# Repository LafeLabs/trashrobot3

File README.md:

# trashrobot3
this is the trash robot that finally pulls the Five Boards into one directory so it's not all over the place

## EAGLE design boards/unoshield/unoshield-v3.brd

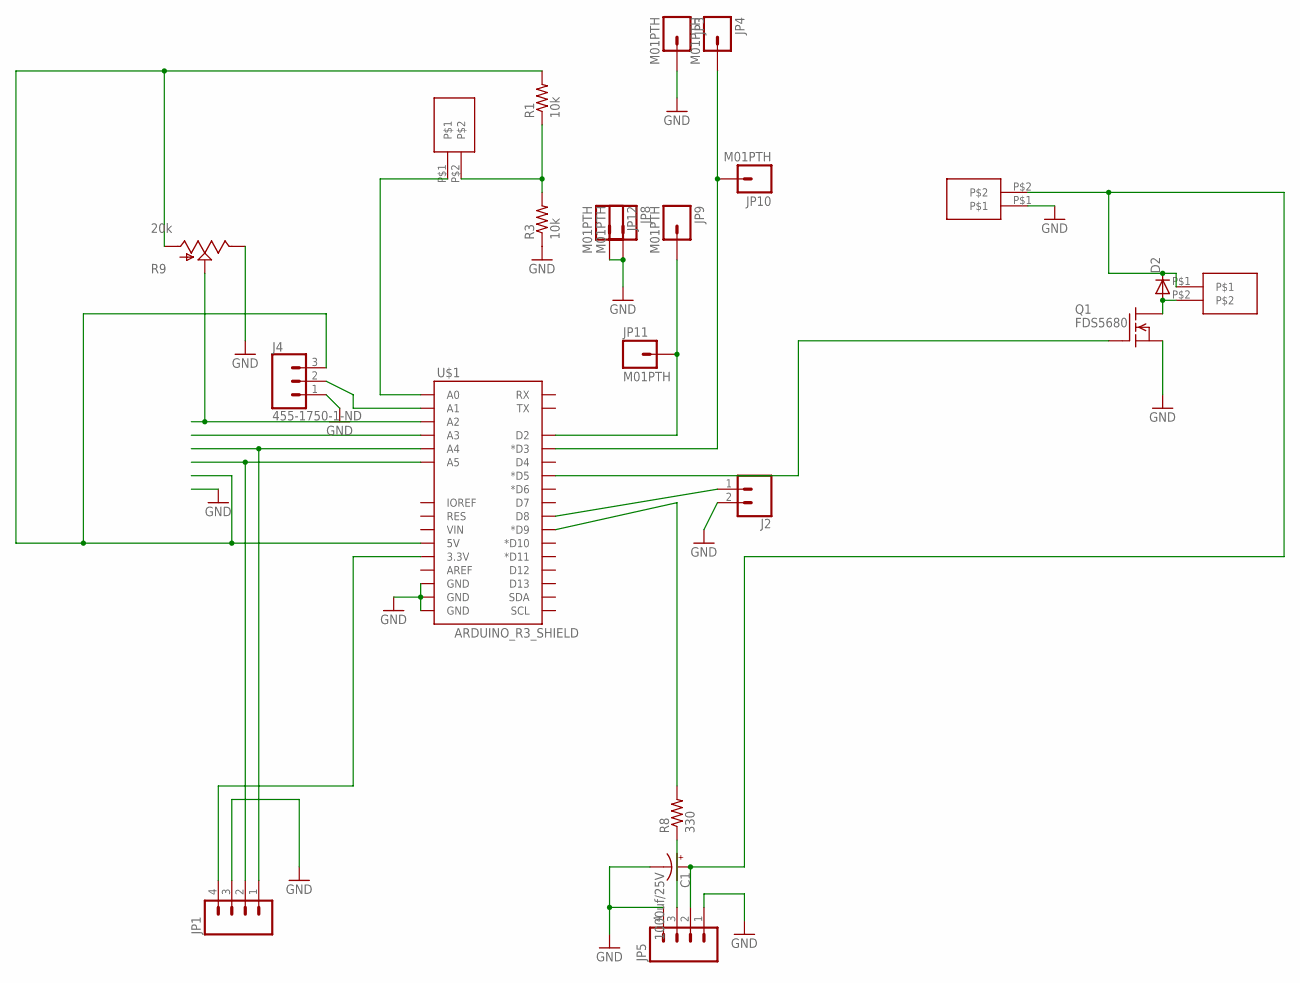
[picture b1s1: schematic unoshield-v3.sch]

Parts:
C1: 1000uf/25V; CPOL-RADIAL-1000UF-25V-KIT
D2: DIODE-DO-214AC; DO-214AC
J2: CONN_02; 1X02
J4: 455-1750-1-ND; 1X03
JP1, JP5: M04PTH; 1X04
JP3, JP4, JP8, JP9, JP10, JP11, JP12: M01PTH; 1X01
Q1: FDS5680; SO-8
R1, R3: 10k; R0603
R8: 330; R0603
R9: 20k; ALPS_POT_KIT
U$1: ARDUINO_R3_SHIELD; UNO_R3_SHIELD
U$6: SPRING-TERMINAL
X1, X2: SPRING-TERMINAL

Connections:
5V: J4.3, R1.2, R9.P$3 (A), U$1.5V
BUTTON: JP4.1, JP10.1, U$1.D3 (*D3)
CL: JP1.2, U$1.A5
DA: JP1.1, U$1.A4
GND: C1.-, J2.2, J4.1, JP1.3, JP3.1, JP5.1, JP5.4, JP8.1, JP12.1, Q1.1 (S), Q1.2 (S), Q1.3 (S), R3.1, R9.P$1 (E), U$1.GND@0 (GND), U$1.GND@1 (GND), U$1.GND@2 (GND), X1.P$1; also elsewhere on the board
unnamed 5: Q1.4 (G), U$1.D5 (*D5); also elsewhere on the board
unnamed: R8.2, U$1.D9 (*D9)
unnamed: R1.1, R3.2, X2.P$2
unnamed: J4.2, U$1.A1
unnamed: D2.A, Q1.5 (D), Q1.6 (D), Q1.7 (D), Q1.8 (D), U$6.P$2
unnamed: JP9.1, JP11.1, U$1.D2
unnamed: J2.1, U$1.D8
unnamed: U$1.A0, X2.P$1
unnamed: JP5.3, R8.1
unnamed: R9.P$2 (S), U$1.A2
VCC: JP1.4, U$1.3.3V
VIN: C1.+, D2.C, JP5.2, U$6.P$1, X1.P$2

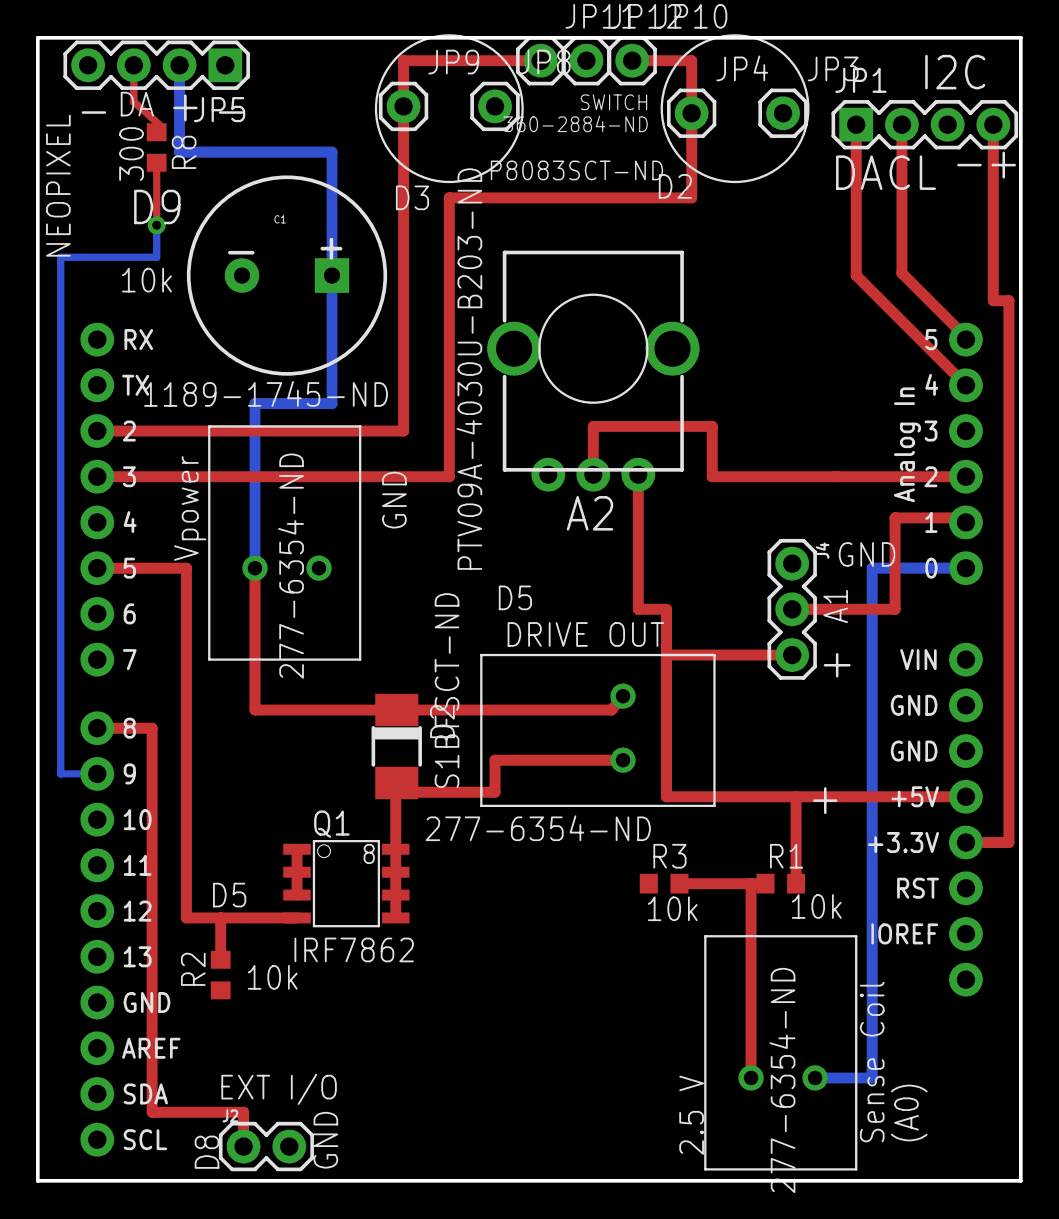
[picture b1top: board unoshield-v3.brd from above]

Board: 2 copper layers, 54.6 x 63.5 mm, 23 parts (0 on the bottom side), 17 nets.

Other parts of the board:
R2: 10k; R0603

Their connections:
GND: R2.1; also elsewhere on the board
unnamed 5: R2.2; also elsewhere on the board

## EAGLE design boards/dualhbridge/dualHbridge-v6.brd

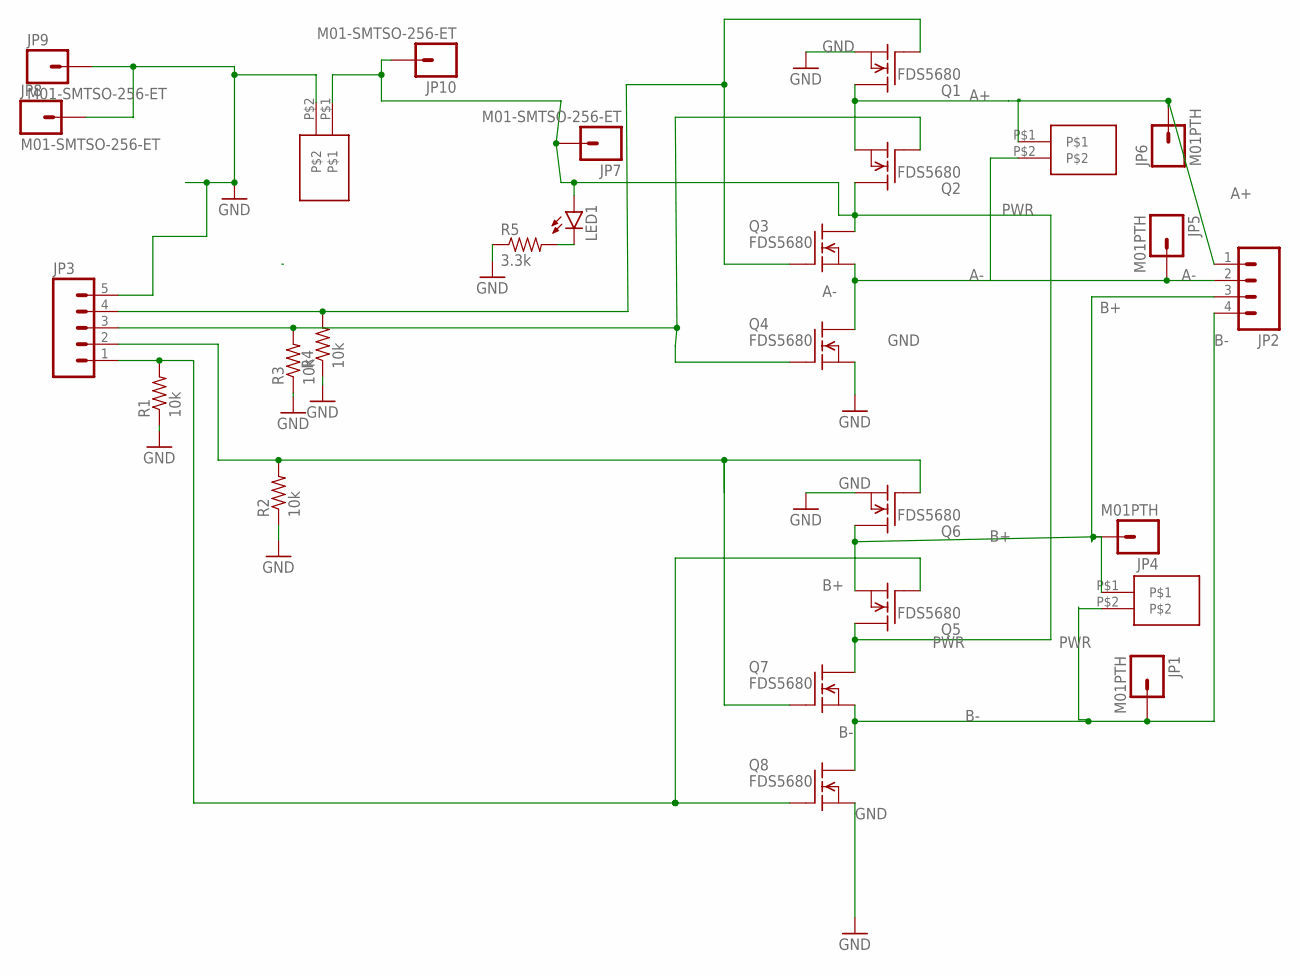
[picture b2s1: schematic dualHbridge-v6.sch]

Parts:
JP1, JP4, JP5, JP6: M01PTH; 1X01@1
JP2: M04LONGPADS; 1X04_LONGPADS
JP3: M05PTH; 1X05
JP7, JP8, JP9, JP10: M01-SMTSO-256-ET; SMTSO-256-ET
LED1: LED5MM
Q1, Q2, Q3, Q4, Q5, Q6, Q7, Q8: FDS5680; SO-8
R1, R2, R3, R4: 10k; 0603-RES
R5: 3.3k; 0603-RES
U$1, U$2, U$3: SPRING-TERMINAL

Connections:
A+: JP2.1, JP6.1, Q1.5 (D), Q1.6 (D), Q1.7 (D), Q1.8 (D), Q2.1 (S), Q2.2 (S), Q2.3 (S), U$1.P$1
A-: JP2.2, JP5.1, Q3.1 (S), Q3.2 (S), Q3.3 (S), Q4.5 (D), Q4.6 (D), Q4.7 (D), Q4.8 (D), U$1.P$2
B+: JP2.3, JP4.1, Q5.1 (S), Q5.2 (S), Q5.3 (S), Q6.5 (D), Q6.6 (D), Q6.7 (D), Q6.8 (D), U$3.P$1
B-: JP1.1, JP2.4, Q7.1 (S), Q7.2 (S), Q7.3 (S), Q8.5 (D), Q8.6 (D), Q8.7 (D), Q8.8 (D), U$3.P$2
GND: JP3.5, JP8.P$1, JP9.P$1, Q1.1 (S), Q1.2 (S), Q1.3 (S), Q4.1 (S), Q4.2 (S), Q4.3 (S), Q6.1 (S), Q6.2 (S), Q6.3 (S), Q8.1 (S), Q8.2 (S), Q8.3 (S), R1.1, R2.1, R3.1, R4.1, R5.1, U$2.P$2
unnamed: JP3.3, Q2.4 (G), Q4.4 (G), R3.2
unnamed: JP3.4, Q1.4 (G), Q3.4 (G), R4.2
unnamed: LED1.K (C), R5.2
unnamed: JP3.2, Q6.4 (G), Q7.4 (G), R2.2
unnamed: JP3.1, Q5.4 (G), Q8.4 (G), R1.2
PWR: JP7.P$1, JP10.P$1, LED1.A, Q2.5 (D), Q2.6 (D), Q2.7 (D), Q2.8 (D), Q3.5 (D), Q3.6 (D), Q3.7 (D), Q3.8 (D), Q5.5 (D), Q5.6 (D), Q5.7 (D), Q5.8 (D), Q7.5 (D), Q7.6 (D), Q7.7 (D), Q7.8 (D), U$2.P$1

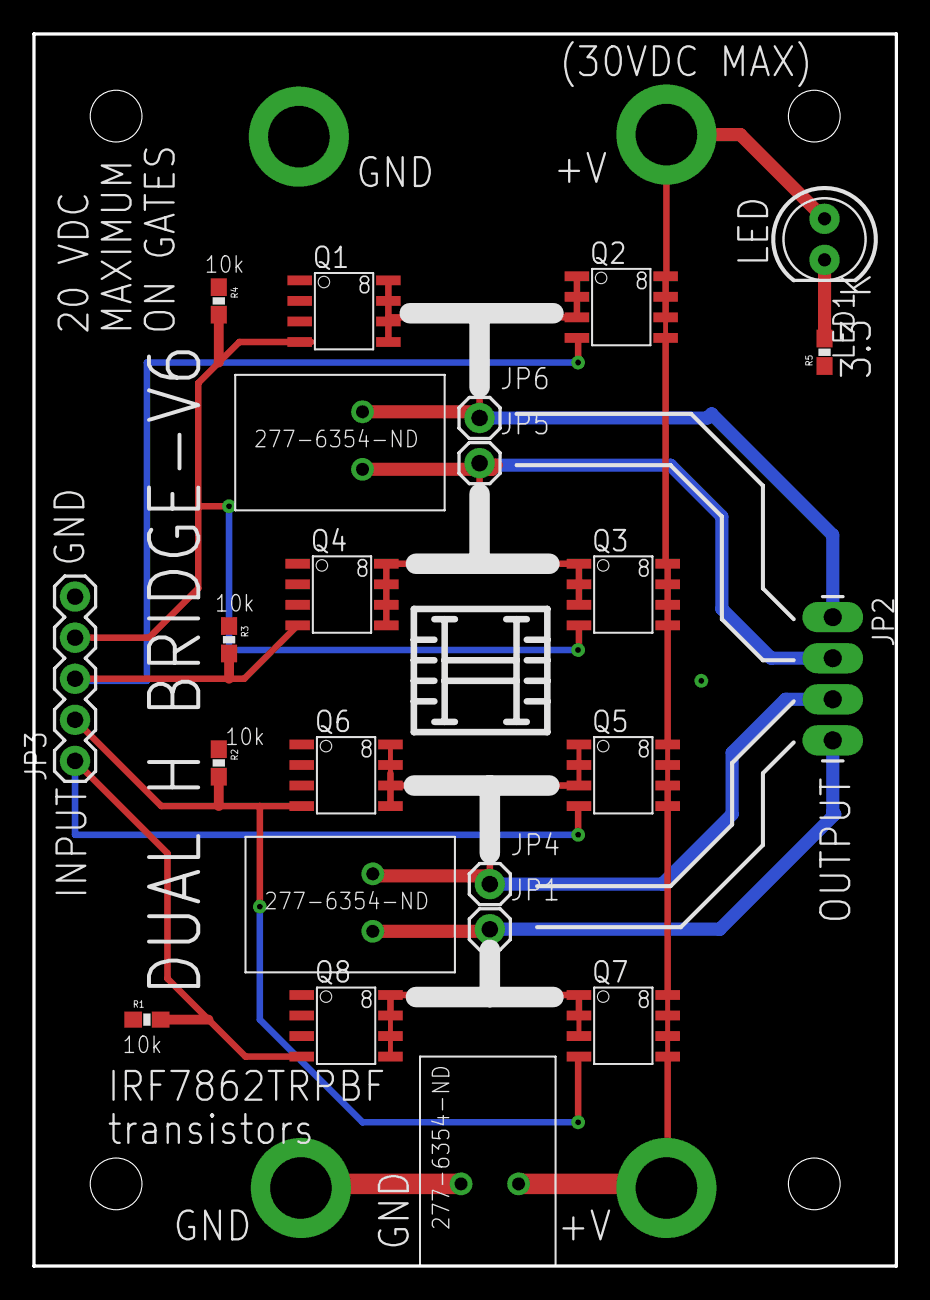
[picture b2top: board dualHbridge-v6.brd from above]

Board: 2 copper layers, 53.3 x 76.2 mm, 27 parts (0 on the bottom side), 11 nets.

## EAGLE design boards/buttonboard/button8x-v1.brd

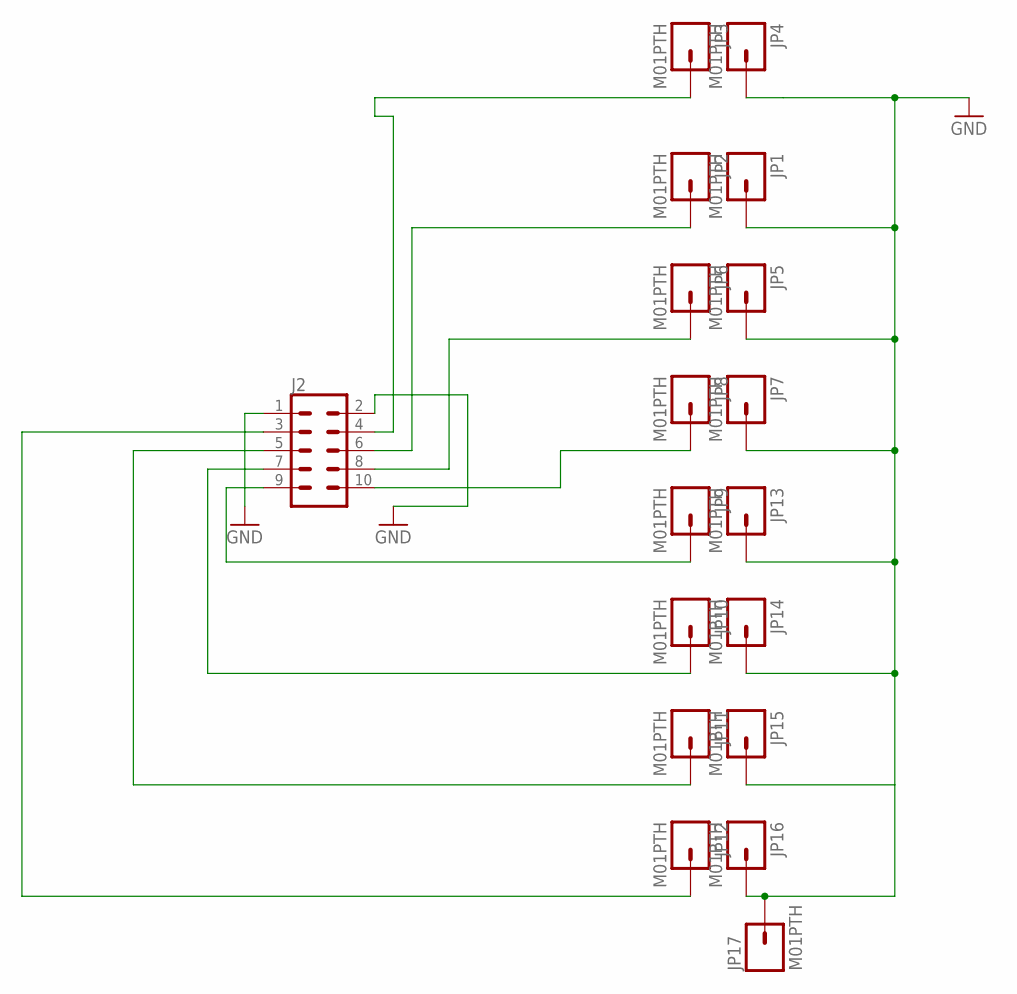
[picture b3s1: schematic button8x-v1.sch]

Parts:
J2: CONN_05X2PTH; 2X5
JP1, JP2, JP3, JP4, JP5, JP6, JP7, JP8, JP9, JP10, JP11, JP12, JP13, JP14, JP15, JP16, JP17: M01PTH; 1X01

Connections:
BUTTON: JP4.1
GND: J2.1, J2.2, JP1.1, JP5.1, JP7.1, JP13.1, JP14.1, JP15.1, JP16.1, JP17.1
unnamed: J2.4, JP3.1
unnamed: J2.6, JP2.1
unnamed: J2.8, JP6.1
unnamed: J2.10, JP8.1
unnamed: J2.9, JP9.1
unnamed: J2.7, JP10.1
unnamed: J2.5, JP11.1
unnamed: J2.3, JP12.1

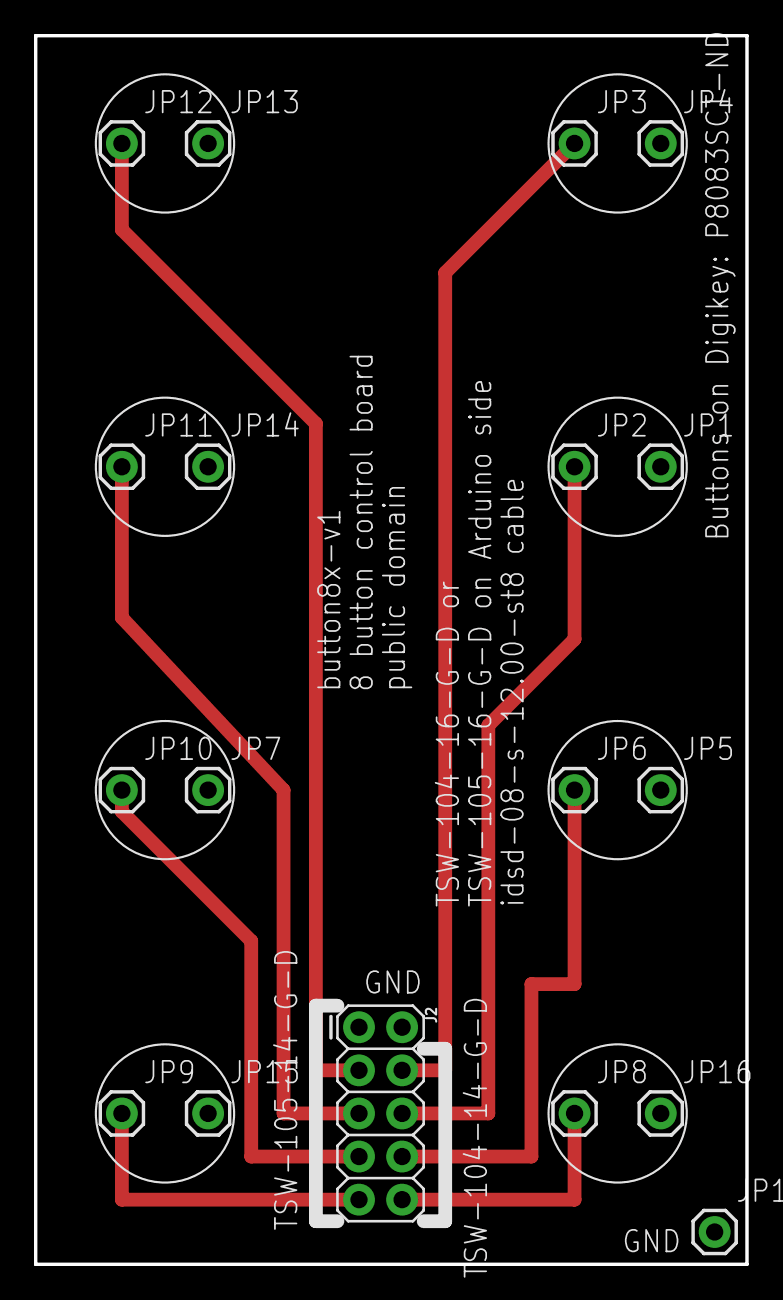
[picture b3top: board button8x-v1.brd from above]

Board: 2 copper layers, 41.9 x 72.4 mm, 18 parts (0 on the bottom side), 9 nets.

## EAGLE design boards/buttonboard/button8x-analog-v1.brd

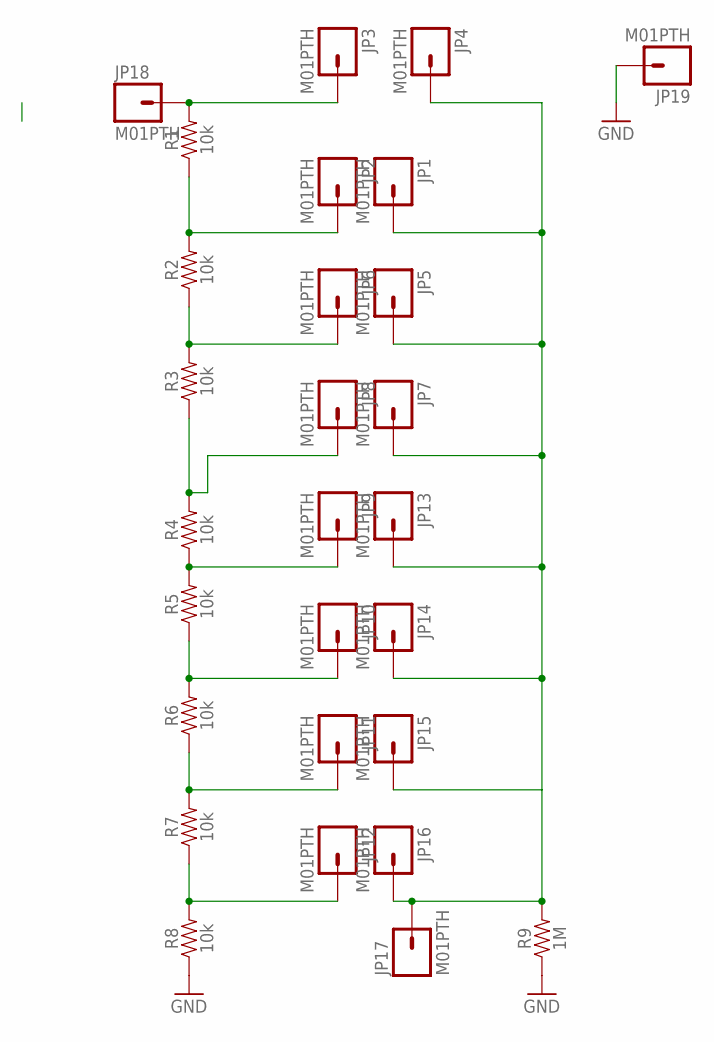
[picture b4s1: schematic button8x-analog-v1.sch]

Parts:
JP1, JP2, JP3, JP4, JP5, JP6, JP7, JP8, JP9, JP10, JP11, JP12, JP13, JP14, JP15, JP16, JP17, JP18, JP19: M01PTH; 1X01
R1, R2, R3, R4, R5, R6, R7, R8: 10k; 0603
R9: 1M; 0603

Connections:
ANALOG: JP1.1, JP4.1, JP5.1, JP7.1, JP13.1, JP14.1, JP15.1, JP16.1, JP17.1, R9.2
GND: JP19.1, R8.1, R9.1
unnamed: JP2.1, R1.1, R2.2
unnamed: JP6.1, R2.1, R3.2
unnamed: JP8.1, R3.1, R4.2
unnamed: JP9.1, R4.1, R5.2
unnamed: JP11.1, R6.1, R7.2
unnamed: JP12.1, R7.1, R8.2
unnamed: JP10.1, R5.1, R6.2
VCC: JP3.1, JP18.1, R1.2

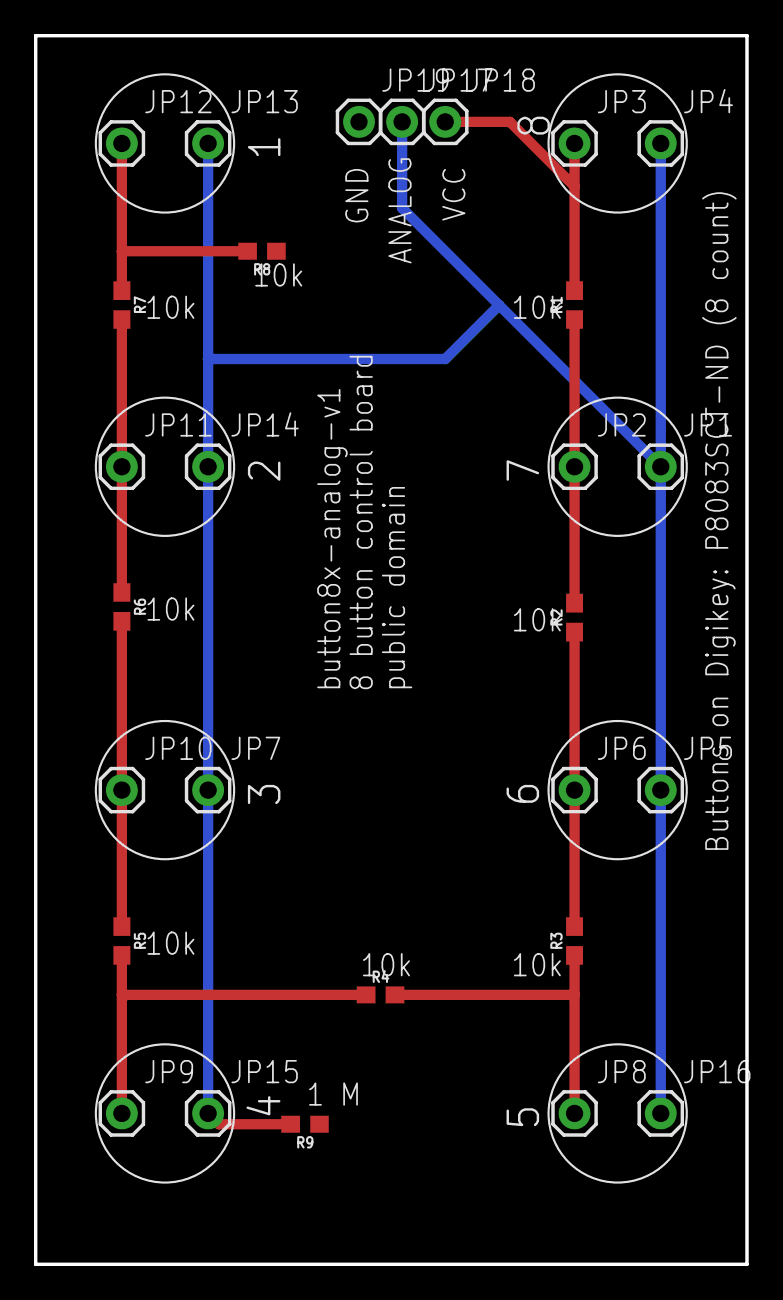
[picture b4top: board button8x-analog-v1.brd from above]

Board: 2 copper layers, 41.9 x 72.4 mm, 28 parts (0 on the bottom side), 10 nets.

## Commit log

2019-03-18 new repo has new button board now, for MEGA only
2019-03-18 all 5 boards now updated with newest versions in this repo, centralized full trash robot
2019-03-18 i dont konw how to do anything with out copying the enitre map factory system so thats what i did here DO NOT MODIFY THAT CODE LOCALLY!!!!11
2019-03-18 working on bom file
2019-03-19 working on bom markdown scroll in scroll/
2019-03-19 working on descriptor scrolls, cloned symbol/ from main mapfactory3
2019-03-19 very small tweaks to boards

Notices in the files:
boards/buttonboard/button8x-analog-v1.brd:
public domain
parts and their libraries:
SparkFun-Connectors: Licensing: Creative Commons ShareAlike 4.0 International - https://creativecommons.org/licenses/by-sa/4.0
